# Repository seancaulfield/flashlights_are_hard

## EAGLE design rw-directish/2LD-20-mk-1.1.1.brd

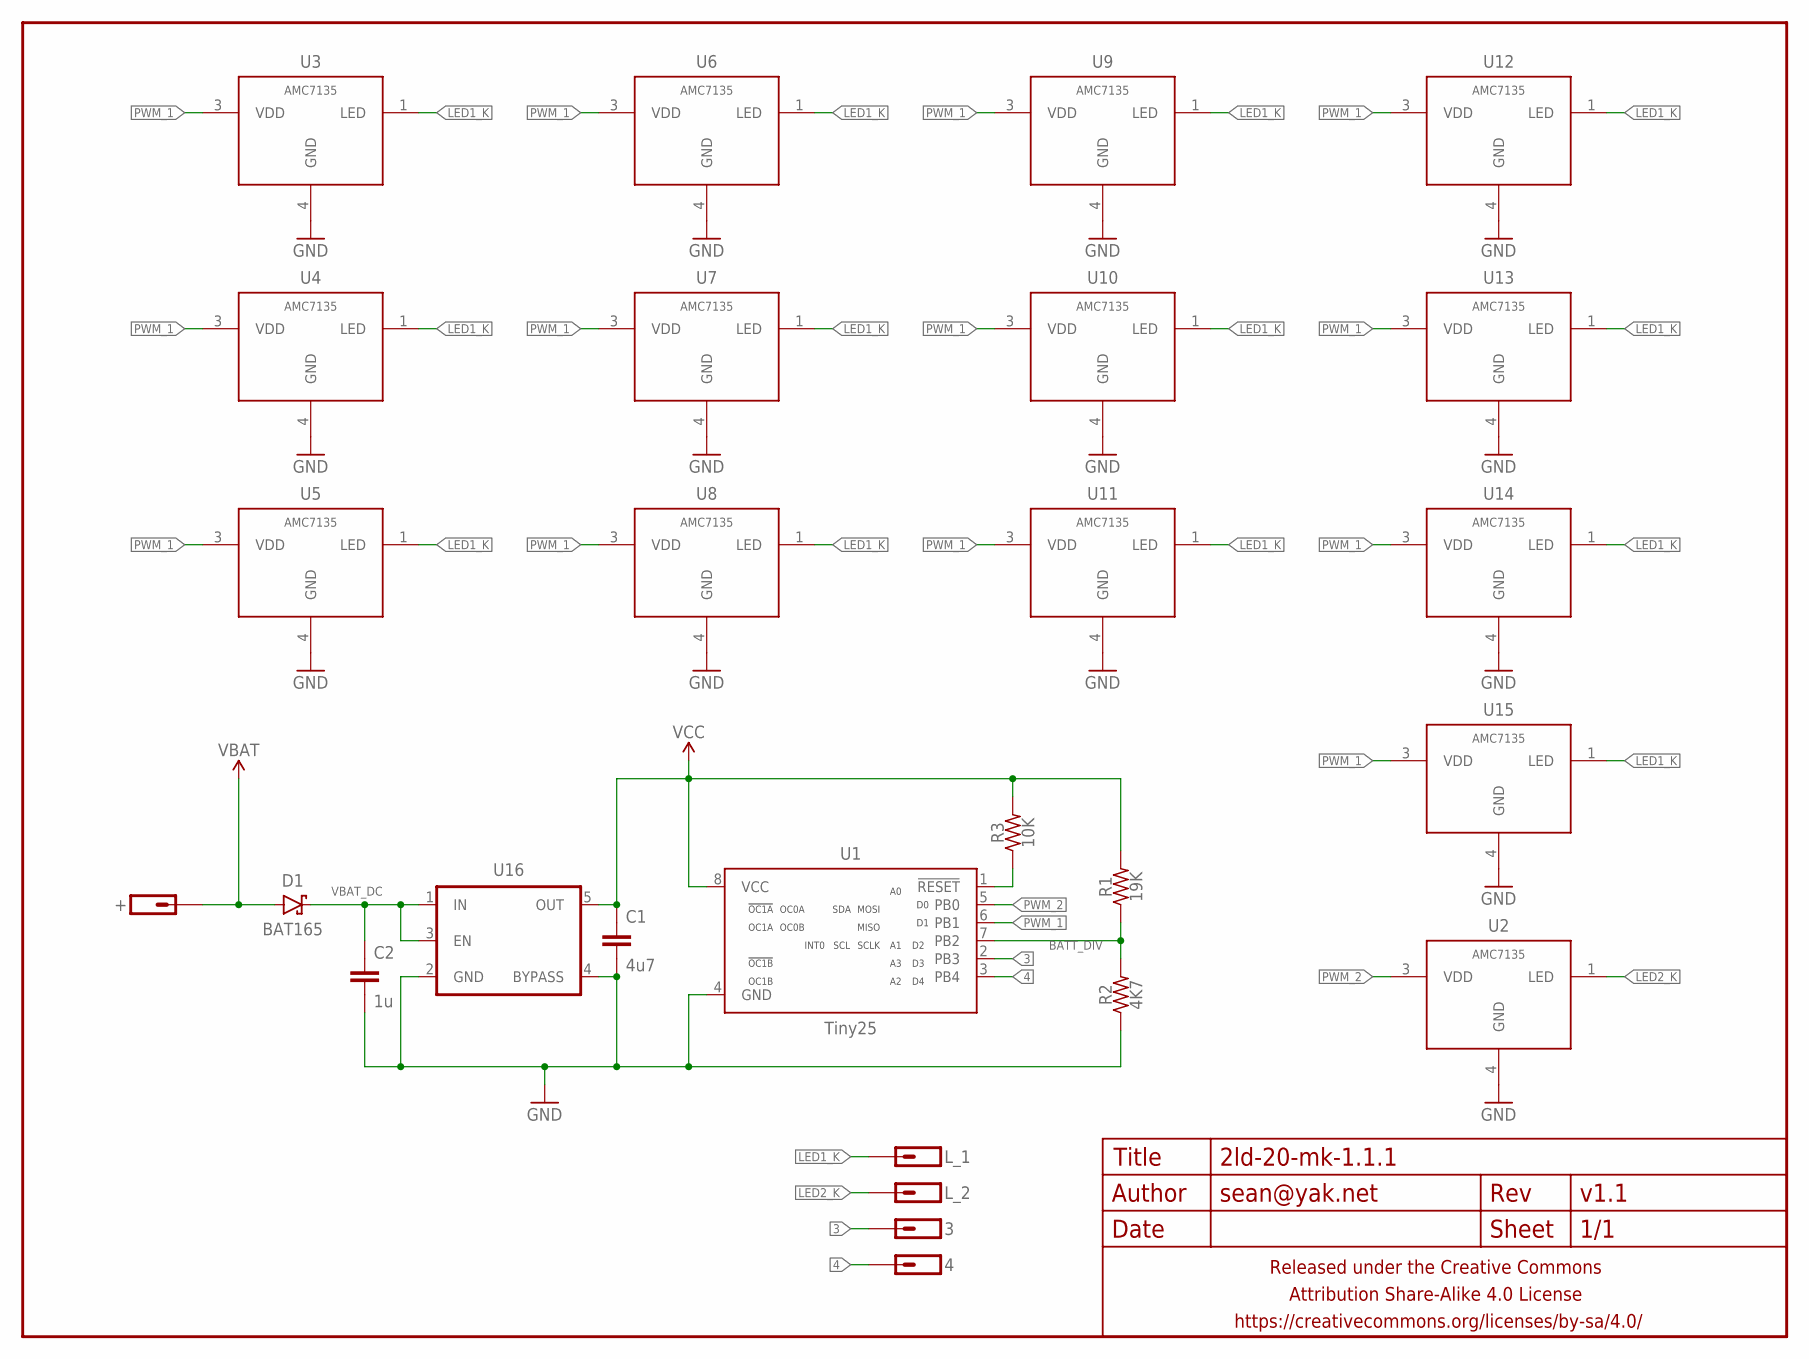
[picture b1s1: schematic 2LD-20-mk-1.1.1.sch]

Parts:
3, 4: M01SMD-0.8MM-DIA-NS; 1X01-SMD-0.8MM-DIA-NS
+: M01PTH-1MM-CIR-NS; 1X01-1MM-CIR-NS
C1: 4u7; C0603-TIGHTER
C2: 1u; C0402
D1: BAT165; SOD323-SCHOTTKY
FRAME1: FRAME-LETTERNO_PACKAGE; DUMMY
L_1: M011X01-0.9MM-CIR; 1X01-0.9MM-CIR
L_2: M01PTH-0.8MM-CIR; 1X01-0.8MM-CIR
R1: 19K; R0402
R2: 4K7; R0402
R3: 10K; R0402
U1: Tiny25; SO08-NARROWER
U2, U3, U4, U5, U6, U7, U8, U9, U10, U11, U12, U13, U14, U15: AMC7135; SOT89-NOTHERM-ROUNDED-LESS
U16: V_REG_SOT-23-5AP2112; SOT23-5

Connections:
3: 3.P$1, U1.2 (PB3)
4: 4.P$1, U1.3 (PB4)
BATT_DIV: R1.1, R2.2, U1.7 (PB2)
GND: C1.2, C2.2, R2.1, U1.4 (GND), U2.4 (GND), U3.4 (GND), U4.4 (GND), U5.4 (GND), U6.4 (GND), U7.4 (GND), U8.4 (GND), U9.4 (GND), U10.4 (GND), U11.4 (GND), U12.4 (GND), U13.4 (GND), U14.4 (GND), U15.4 (GND), U16.2 (GND), U16.4 (BYPASS)
LED1_K: L_1.P$1, U3.1 (LED), U4.1 (LED), U5.1 (LED), U6.1 (LED), U7.1 (LED), U8.1 (LED), U9.1 (LED), U10.1 (LED), U11.1 (LED), U12.1 (LED), U13.1 (LED), U14.1 (LED), U15.1 (LED)
LED2_K: L_2.1, U2.1 (LED)
unnamed: R3.1, U1.1 (!RESET)
PWM_1: U1.6 (PB1), U3.3 (VDD), U4.3 (VDD), U5.3 (VDD), U6.3 (VDD), U7.3 (VDD), U8.3 (VDD), U9.3 (VDD), U10.3 (VDD), U11.3 (VDD), U12.3 (VDD), U13.3 (VDD), U14.3 (VDD), U15.3 (VDD)
PWM_2: U1.5 (PB0), U2.3 (VDD)
VBAT: +.1, D1.A
VBAT_DC: C2.1, D1.C, U16.1 (IN), U16.3 (EN)
VCC: C1.1, R1.2, R3.2, U1.8 (VCC), U16.5 (OUT)

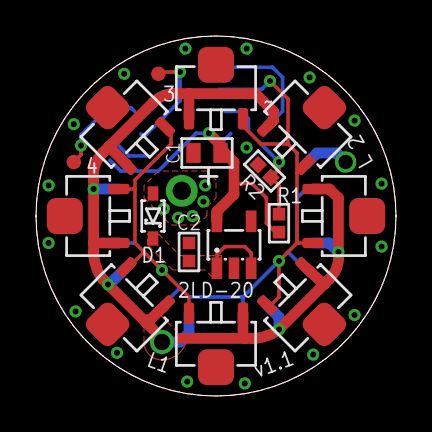
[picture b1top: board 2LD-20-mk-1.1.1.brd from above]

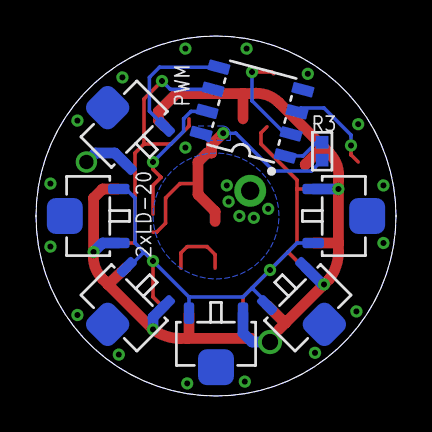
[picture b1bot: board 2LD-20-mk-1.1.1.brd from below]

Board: 2 copper layers, 20.0 x 20.0 mm, 28 parts (8 on the bottom side), 12 nets.

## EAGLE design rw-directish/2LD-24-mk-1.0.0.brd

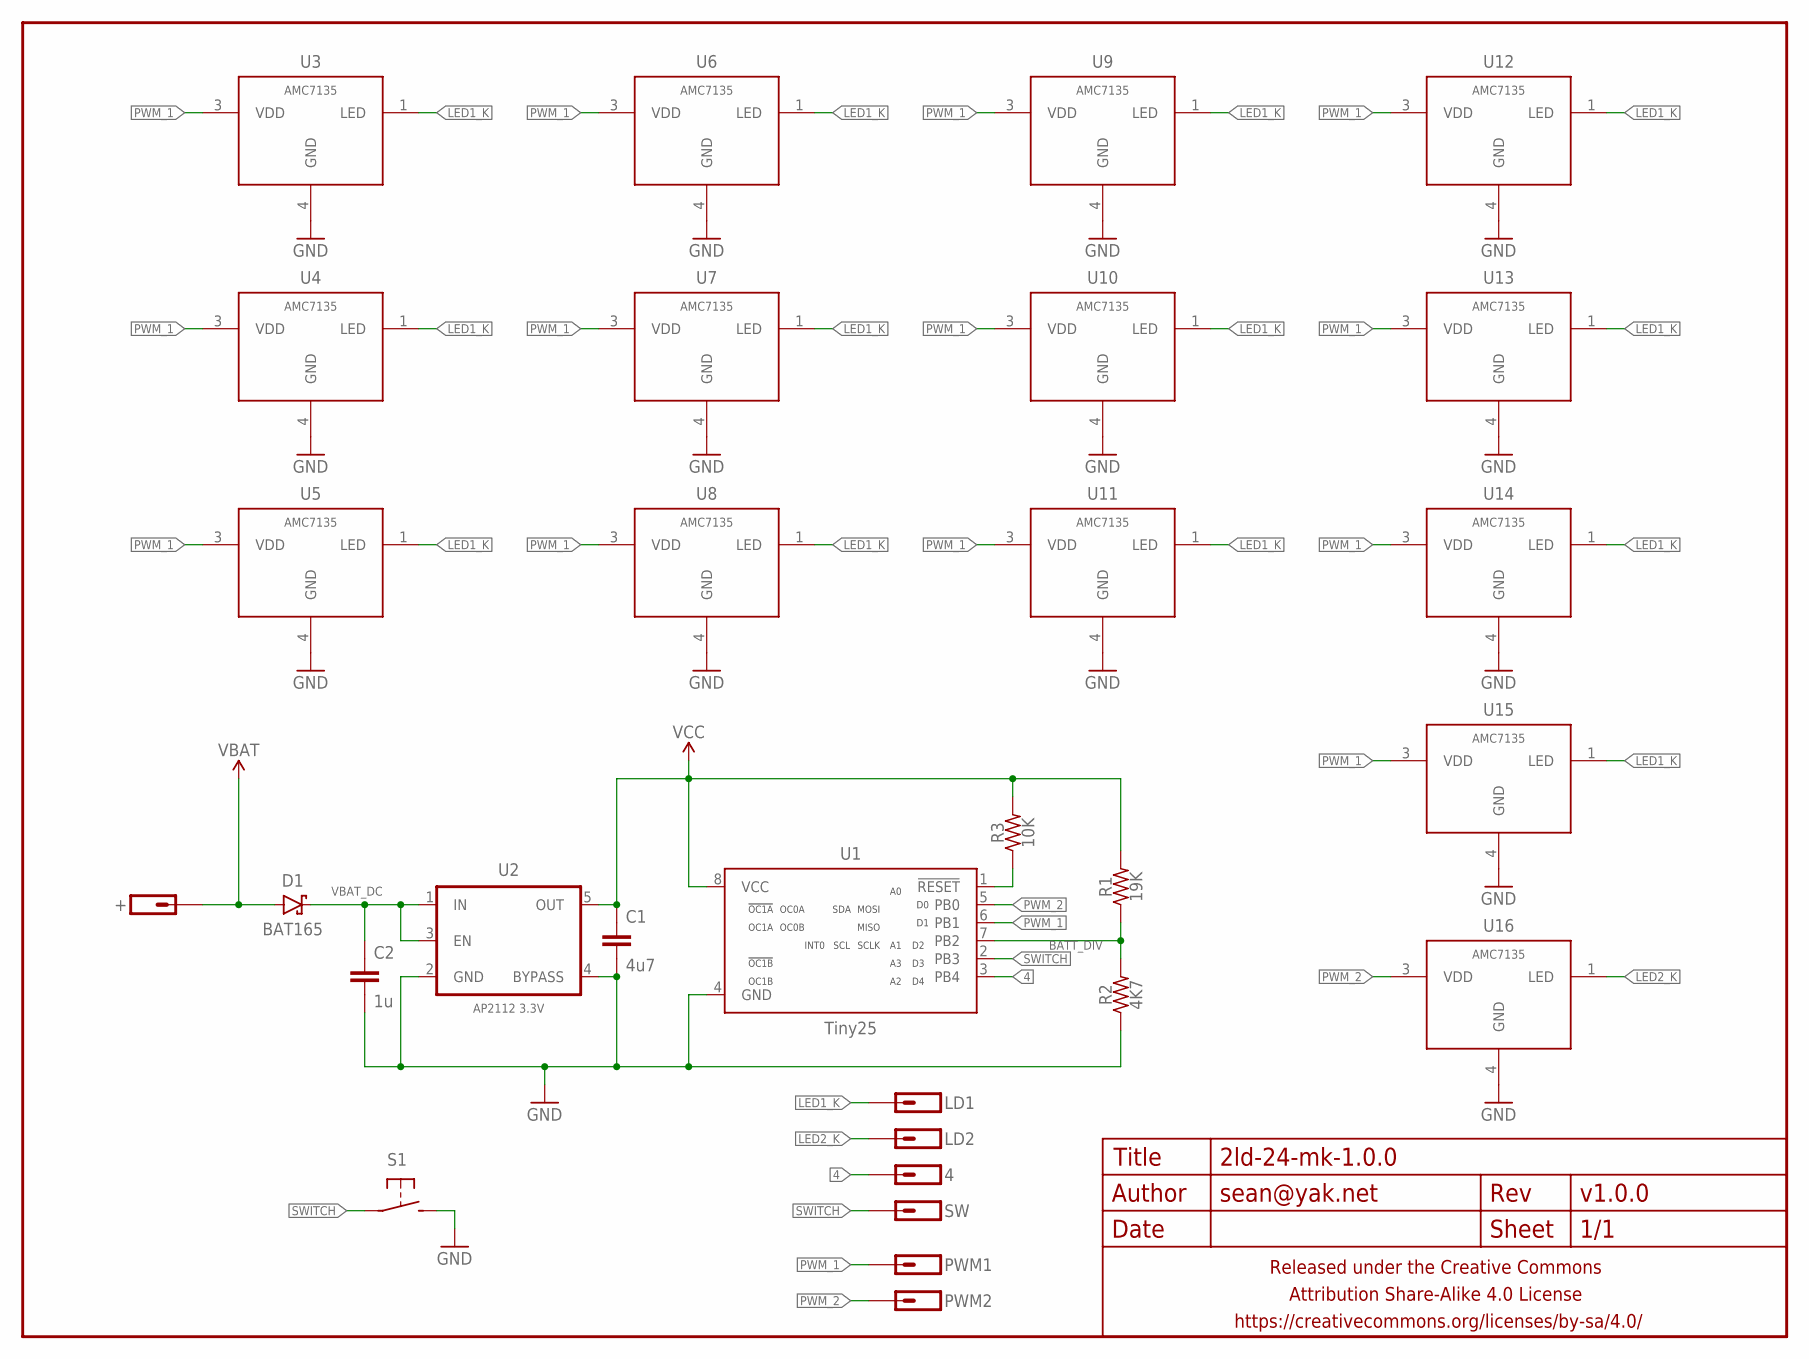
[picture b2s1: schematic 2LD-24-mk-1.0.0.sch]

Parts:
4: M01SMD-0.8MM-DIA-NS; 1X01-SMD-0.8MM-DIA-NS
+: M01PTH-1MM-CIR-NS; 1X01-1MM-CIR-NS
C1: 4u7; C0603-TIGHTER
C2: 1u; C0603-TIGHTER
D1: BAT165; SOD323-SCHOTTKY
FRAME1: FRAME-LETTERNO_PACKAGE; DUMMY
LD1: M01PTH-1MM-CIR-NS; 1X01-1MM-CIR-NS
LD2: M01PTH-0.8MM-CIR; 1X01-0.8MM-CIR
PWM1, PWM2: M01SMD-0.8MM-DIA-NS; 1X01-SMD-0.8MM-DIA-NS
R1: 19K; R0603-TIGHTER
R2: 4K7; R0603-TIGHTER
R3: 10K; R0603-TIGHTER
S1: SPST-NO-TACT3MM-RA-SMALLER; TACTILE-PTH-SIDE-SMALLER
SW: M01SMD-0.8MM-DIA-NS; 1X01-SMD-0.8MM-DIA-NS
U1: Tiny25; SO08-NARROWER
U2: AP2112 3.3V; SOT23-5-SLIM
U3, U4, U5, U6, U7, U8, U9, U10, U11, U12, U13, U14, U15, U16: AMC7135; SOT89-NOTHERM-ROUNDED-LESS

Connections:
4: 4.P$1, U1.3 (PB4)
BATT_DIV: R1.1, R2.2, U1.7 (PB2)
GND: C1.2, C2.2, R2.1, S1.2, U1.4 (GND), U2.2 (GND), U2.4 (BYPASS), U3.4 (GND), U4.4 (GND), U5.4 (GND), U6.4 (GND), U7.4 (GND), U8.4 (GND), U9.4 (GND), U10.4 (GND), U11.4 (GND), U12.4 (GND), U13.4 (GND), U14.4 (GND), U15.4 (GND), U16.4 (GND)
LED1_K: LD1.1, U3.1 (LED), U4.1 (LED), U5.1 (LED), U6.1 (LED), U7.1 (LED), U8.1 (LED), U9.1 (LED), U10.1 (LED), U11.1 (LED), U12.1 (LED), U13.1 (LED), U14.1 (LED), U15.1 (LED)
LED2_K: LD2.1, U16.1 (LED)
unnamed: R3.1, U1.1 (!RESET)
PWM_1: PWM1.P$1, U1.6 (PB1), U3.3 (VDD), U4.3 (VDD), U5.3 (VDD), U6.3 (VDD), U7.3 (VDD), U8.3 (VDD), U9.3 (VDD), U10.3 (VDD), U11.3 (VDD), U12.3 (VDD), U13.3 (VDD), U14.3 (VDD), U15.3 (VDD)
PWM_2: PWM2.P$1, U1.5 (PB0), U16.3 (VDD)
SWITCH: S1.1, SW.P$1, U1.2 (PB3)
VBAT: +.1, D1.A
VBAT_DC: C2.1, D1.C, U2.1 (IN), U2.3 (EN)
VCC: C1.1, R1.2, R3.2, U1.8 (VCC), U2.5 (OUT)

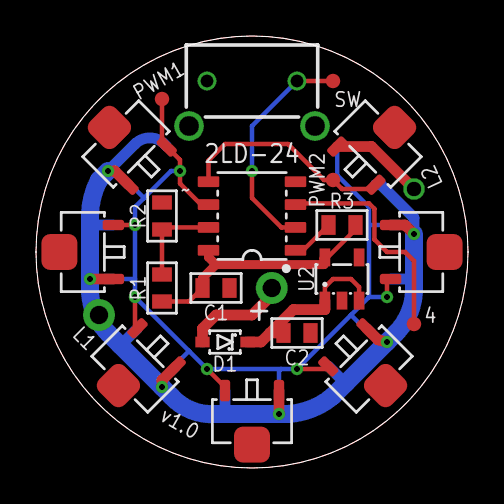
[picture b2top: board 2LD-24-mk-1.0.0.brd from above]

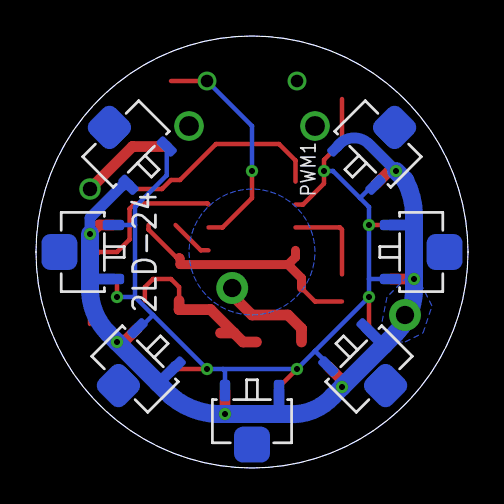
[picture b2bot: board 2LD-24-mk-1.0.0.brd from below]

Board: 2 copper layers, 24.0 x 24.0 mm, 31 parts (7 on the bottom side), 12 nets.

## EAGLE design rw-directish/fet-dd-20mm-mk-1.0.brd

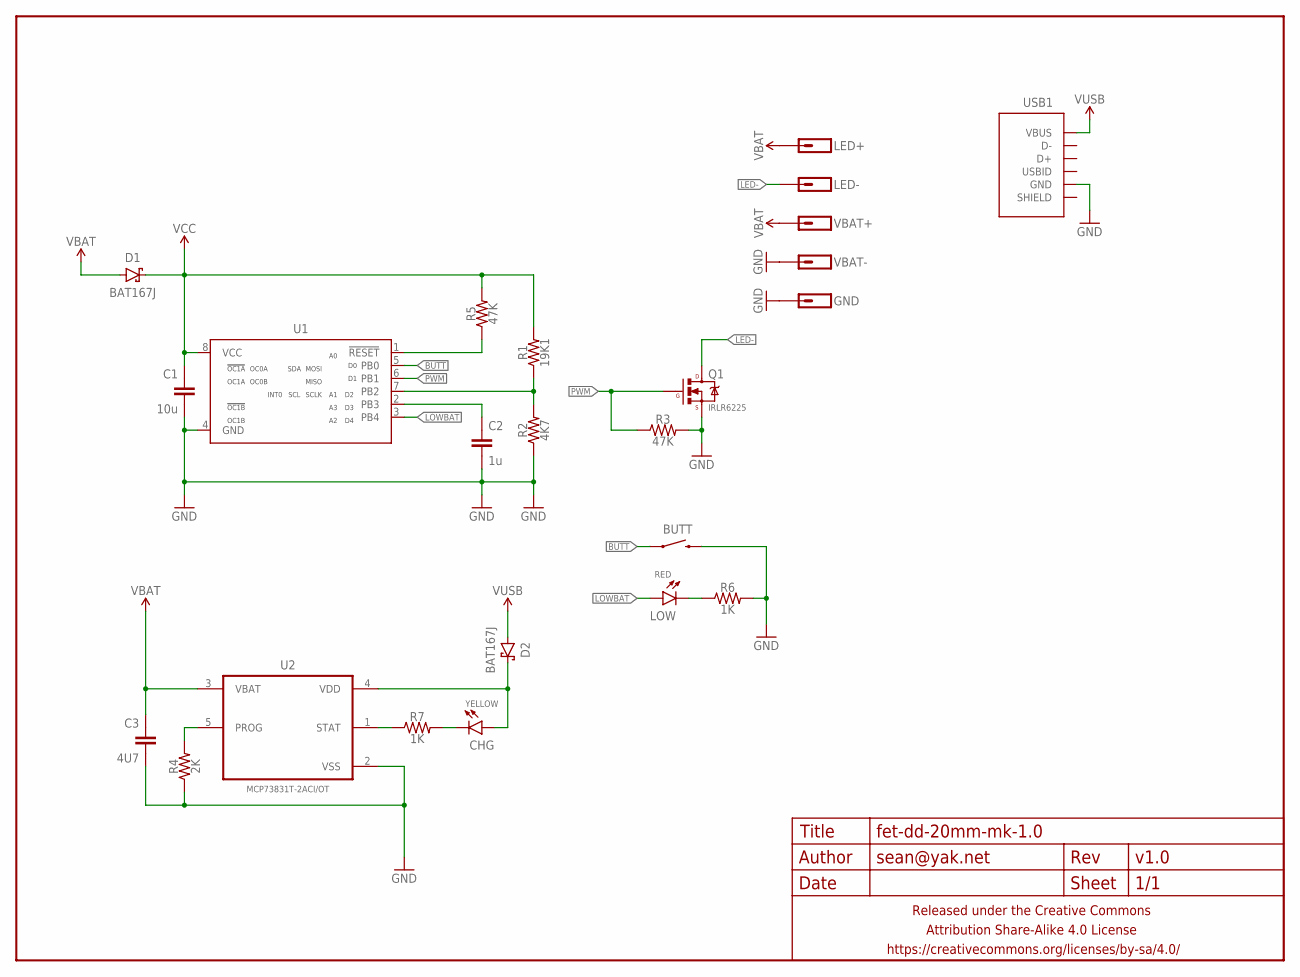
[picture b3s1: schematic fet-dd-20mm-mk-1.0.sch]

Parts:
BUTT: SWITCH-MOMENTARY-2PTH-RA; TACTILE-PTH-SIDE
C1: 10u; C0603-TIGHTER
C2: 1u; C0603-TIGHTER
C3: 4U7; C0603-TIGHTER
CHG: YELLOW; LED-0603-TIGHT
D1, D2: BAT167J; SOD323-SCHOTTKY
FRAME1: FRAME-LETTERNO_PACKAGE; DUMMY
GND: M01PTH_2MM; 1X01_2MM
LED+: M01PTH_2MM; 1X01_2MM
LED-: M01PTH_2MM; 1X01_2MM
LOW: RED; LED-0603-TIGHT
Q1: IRLR6225; SOT223-CLOSER
R1: 19K1; R0603-TIGHTER
R2: 4K7; R0603-TIGHTER
R3, R5: 47K; R0402
R4: 2K; R0603-TIGHTER
R6, R7: 1K; R0603-TIGHTER
U1: ATTINY13SOIC-NARROWPADS; SO08-NARROWER
U2: MCP73831T-2ACI/OT; SOT95P280X145-5N
USB1: USB-AB-SHIELDFCI-10118193-USB-MICRO-B; FCI-10118193-USB-MICRO-B
VBAT+: M01NOSTOP-CANTSTOP-DONTKNOWHOWTOSTOP; 1X01_SMD_NOSTOP_NOSILK
VBAT-: M01NOT-A-VIA-NOPE; 1X01_NOSILK_NOSTOP

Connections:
BUTT: BUTT.1, U1.5 (PB0)
GND: BUTT.2, C1.2, C2.2, C3.2, GND.1, Q1.3 (S), R2.1, R3.2, R4.1, R6.2, U1.4 (GND), U2.2 (VSS), USB1.5 (GND), VBAT-.P$1
LED-: LED-.1, Q1.2 (D), Q1.4 (D)
LOWBAT: LOW.A, U1.3 (PB4)
unnamed: R5.1, U1.1 (!RESET)
unnamed: R1.1, R2.2, U1.7 (PB2)
unnamed: C2.1, U1.2 (PB3)
unnamed: R4.2, U2.5 (PROG)
unnamed: CHG.A, D2.C, U2.4 (VDD)
unnamed: LOW.C, R6.1
unnamed: CHG.C, R7.2
unnamed: R7.1, U2.1 (STAT)
PWM: Q1.1 (G), R3.1, U1.6 (PB1)
VBAT: C3.1, D1.A, LED+.1, U2.3 (VBAT), VBAT+.1
VCC: C1.1, D1.C, R1.2, R5.2, U1.8 (VCC)
VUSB: D2.A, USB1.1 (VBUS)

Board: 2 copper layers, 25 parts (1 on the bottom side), 16 nets, no tracks yet.

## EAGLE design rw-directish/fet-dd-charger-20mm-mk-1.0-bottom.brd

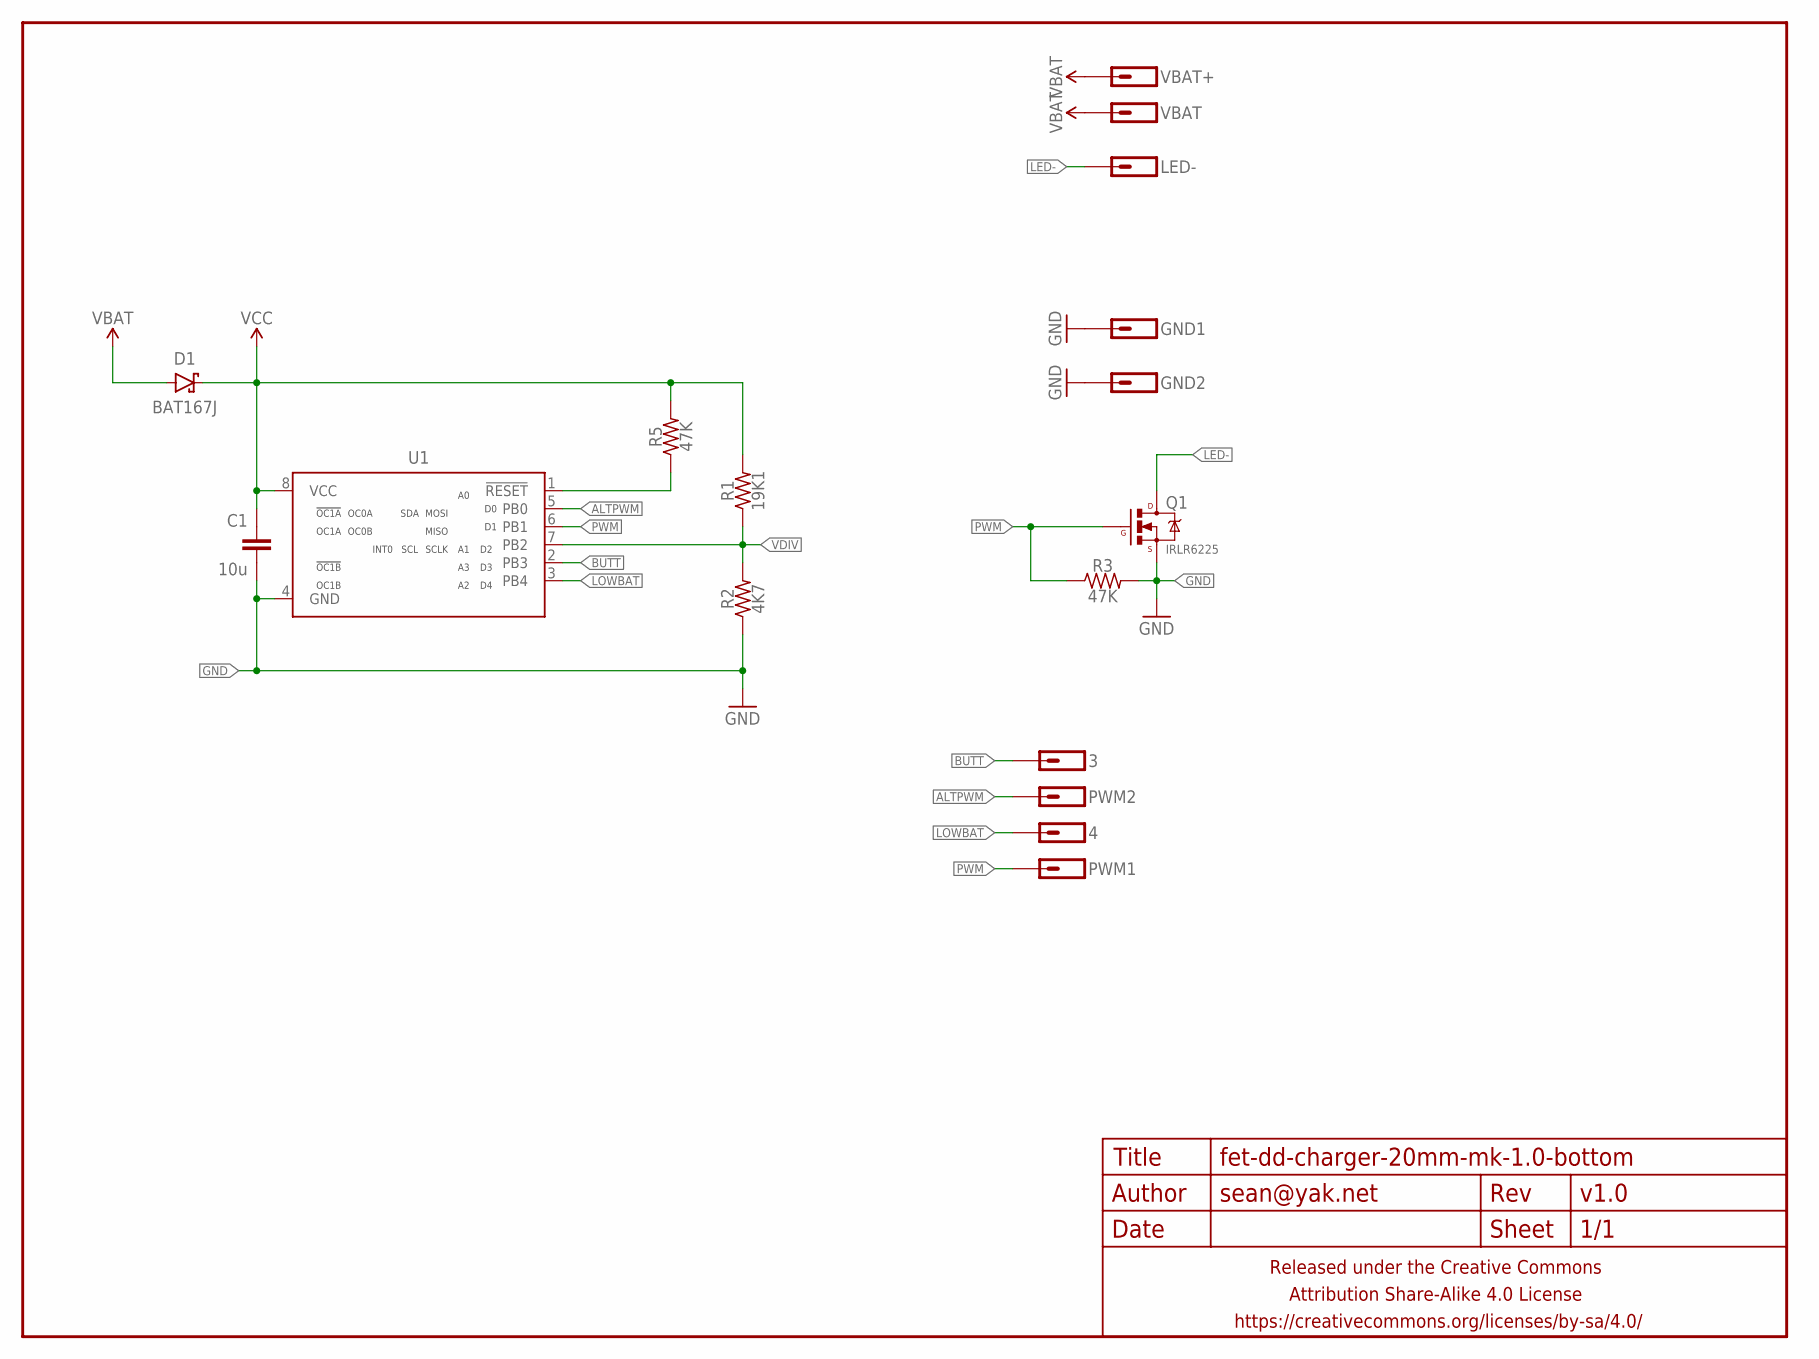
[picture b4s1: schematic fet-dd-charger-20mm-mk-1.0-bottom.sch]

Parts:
3, 4: M01SMD-1MM-DIA-NS; 1X01-SMD-1MM-DIA-NS
C1: 10u; C0603-TIGHTER
D1: BAT167J; SOD123-SCHOTTKY
FRAME1: FRAME-LETTERNO_PACKAGE; DUMMY
GND1, GND2: M01PTH_2MM; 1X01_2MM
LED-: M01PTH_2MM; 1X01_2MM
PWM1, PWM2: M01SMD-1MM-DIA-NS; 1X01-SMD-1MM-DIA-NS
Q1: IRLR6225; POWERPACK-SO-8
R1: 19K1; R0603-TIGHTER
R2: 4K7; R0603-TIGHTER
R3, R5: 47K; R0603-TIGHTER
U1: ATTINY13SOIC-NARROWPADS; SO08-NARROWER
VBAT: M01PTH_2MM; 1X01_2MM
VBAT+: M01NOSTOP-CANTSTOP-DONTKNOWHOWTOSTOP; 1X01_SMD_NOSTOP_NOSILK

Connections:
ALTPWM: PWM2.P$1, U1.5 (PB0)
BUTT: 3.P$1, U1.2 (PB3)
GND: C1.2, GND1.1, GND2.1, Q1.1 (S), Q1.2 (S), Q1.3 (S), R2.1, R3.2, U1.4 (GND)
LED-: LED-.1, Q1.5678 (D)
LOWBAT: 4.P$1, U1.3 (PB4)
unnamed: R5.1, U1.1 (!RESET)
PWM: PWM1.P$1, Q1.4 (G), R3.1, U1.6 (PB1)
VBAT: D1.A, VBAT.1, VBAT+.1
VCC: C1.1, D1.C, R1.2, R5.2, U1.8 (VCC)
VDIV: R1.1, R2.2, U1.7 (PB2)

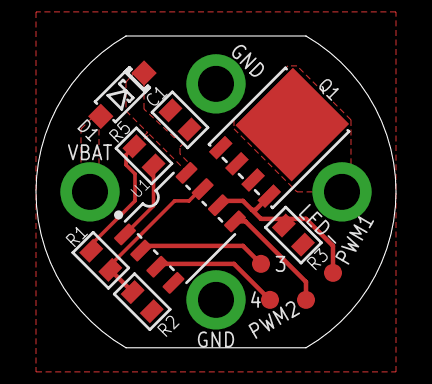
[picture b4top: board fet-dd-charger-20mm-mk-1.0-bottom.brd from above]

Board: 2 copper layers, 20.0 x 17.3 mm, 18 parts (1 on the bottom side), 10 nets.

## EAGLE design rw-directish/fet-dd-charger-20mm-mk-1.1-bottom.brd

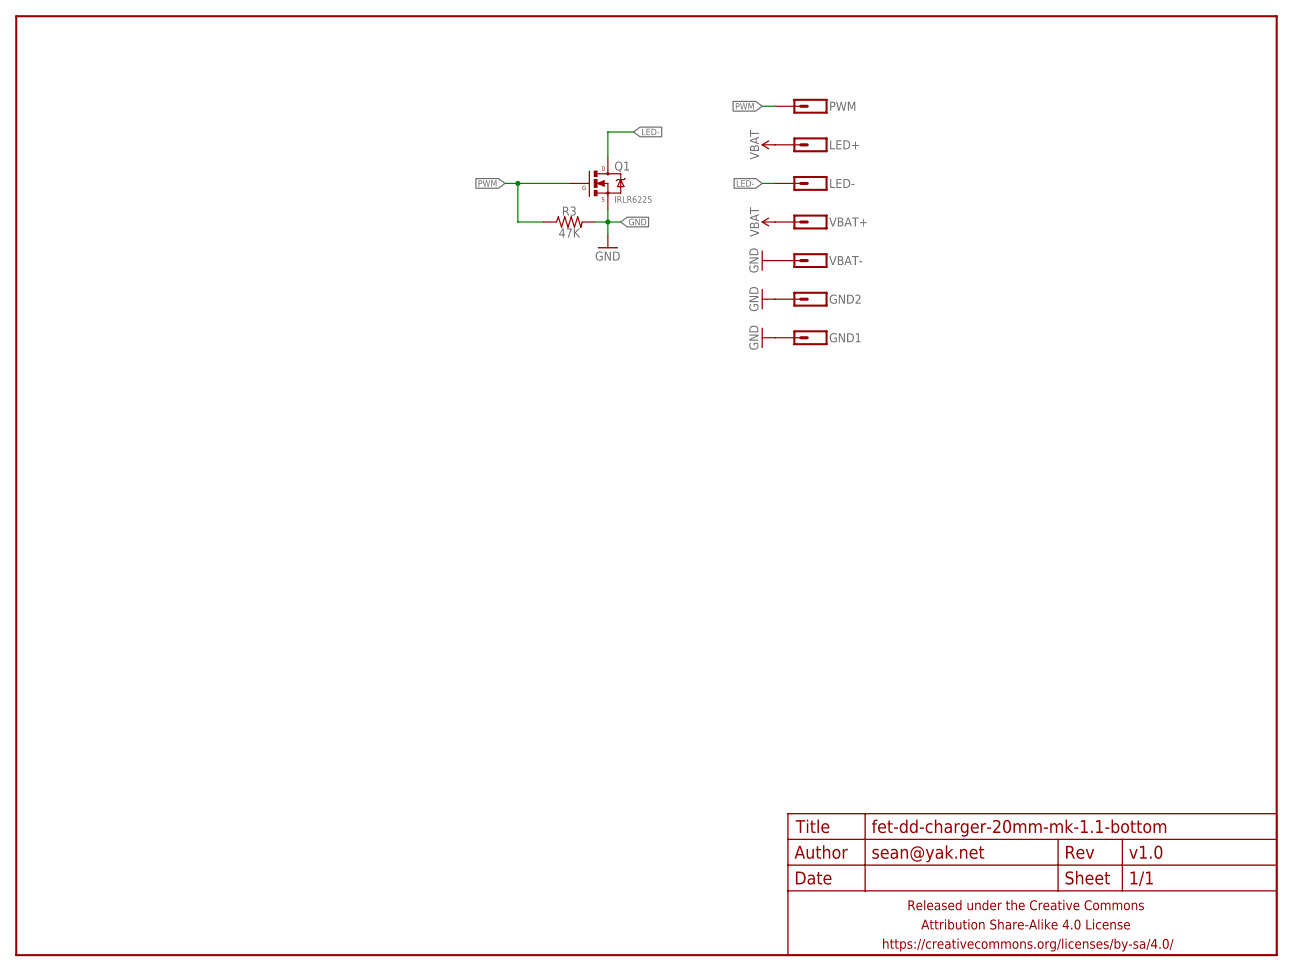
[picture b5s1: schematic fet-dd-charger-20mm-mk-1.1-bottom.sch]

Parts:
FRAME1: FRAME-LETTERNO_PACKAGE; DUMMY
GND1, GND2: M01PTH_2MM; 1X01_2MM
LED+: M01PTH_2MM; 1X01_2MM
LED-: M01PTH_2MM; 1X01_2MM
PWM: M01SMD-1MM-CIR; 1X01-SMD-1MM-DIA
Q1: IRLR6225; SOT223-CLOSER
R3: 47K; R0603-TIGHTER
VBAT+: M01NOSTOP-CANTSTOP-DONTKNOWHOWTOSTOP; 1X01_SMD_NOSTOP_NOSILK
VBAT-: M01NOT-A-VIA-NOPE; 1X01_NOSILK_NOSTOP

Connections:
GND: GND1.1, GND2.1, Q1.3 (S), R3.2, VBAT-.P$1
LED-: LED-.1, Q1.2 (D), Q1.4 (D)
PWM: PWM.P$1, Q1.1 (G), R3.1
VBAT: LED+.1, VBAT+.1

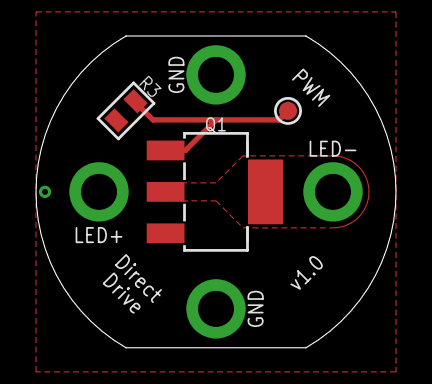
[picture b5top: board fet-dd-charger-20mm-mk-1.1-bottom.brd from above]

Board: 2 copper layers, 20.0 x 17.3 mm, 10 parts (1 on the bottom side), 4 nets.

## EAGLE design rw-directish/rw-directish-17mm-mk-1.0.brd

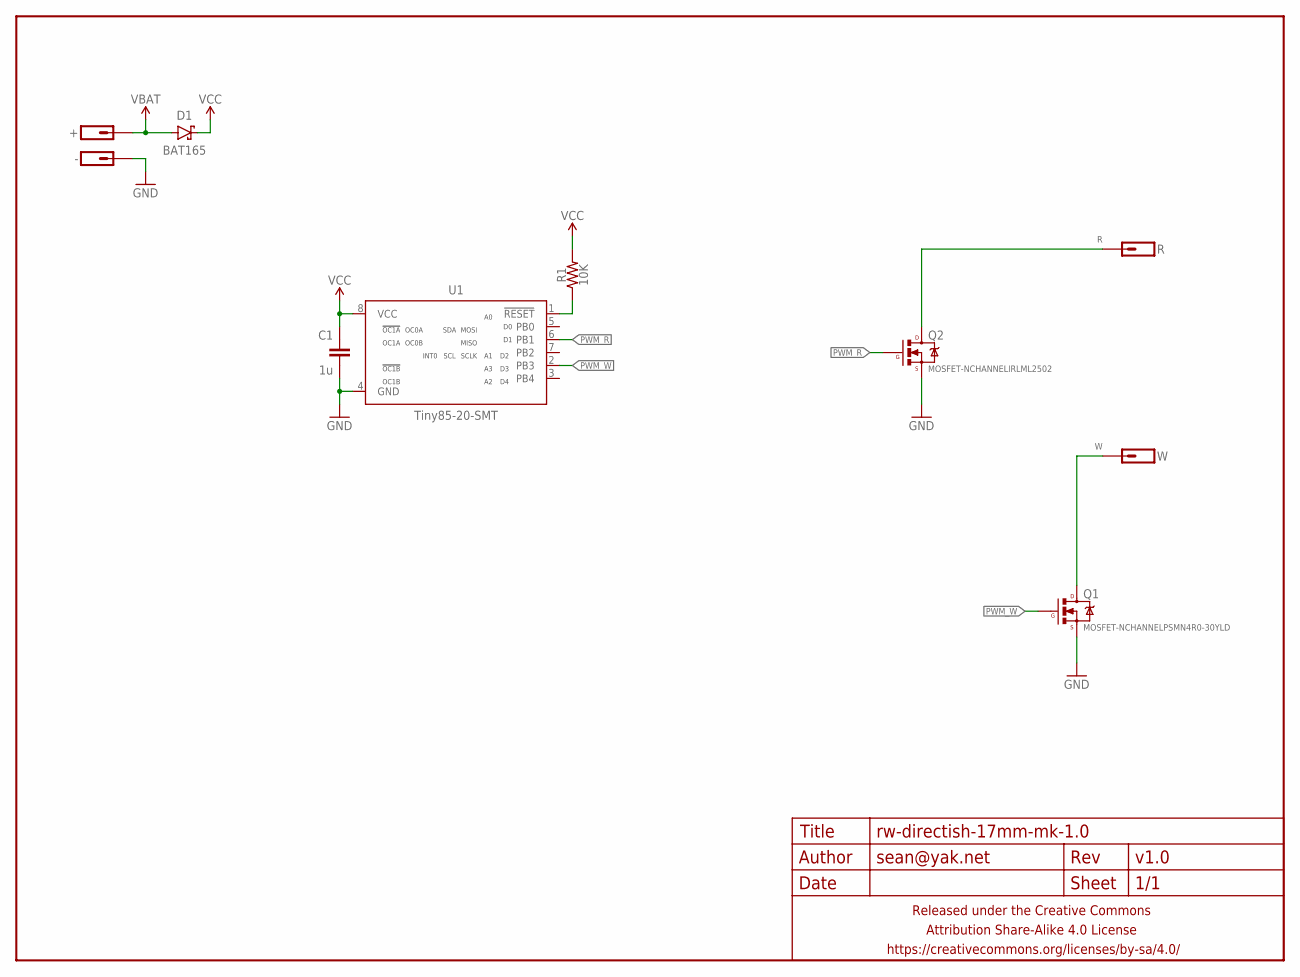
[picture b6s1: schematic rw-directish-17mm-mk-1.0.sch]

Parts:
+: M01PTH-1.2MM-NS; 1X01-1.2MM-NS
-: M01NOT-A-VIA-NOPE; 1X01_NOSILK_NOSTOP
C1: 1u; C0402
D1: BAT165; SOD323-SCHOTTKY
FRAME1: FRAME-LETTERNO_PACKAGE; DUMMY
Q1: MOSFET-NCHANNELPSMN4R0-30YLD; LFPAK56
Q2: MOSFET-NCHANNELIRLML2502; SOT23
R: M01SMD-1.25MM-DIA; 1X01-SMD-1.25MM-DIA-NS
R1: 10K; R0402
U1: Tiny85-20-SMT; SO08-EIAJ
W: M01SMD-1.25MM-DIA; 1X01-SMD-1.25MM-DIA-NS

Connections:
GND: -.P$1, C1.2, Q1.1 (S), Q1.2 (S), Q1.3 (S), Q2.2 (S), U1.4 (GND)
unnamed: R1.1, U1.1 (!RESET)
PWM_R: Q2.1 (G), U1.6 (PB1)
PWM_W: Q1.4 (G), U1.2 (PB3)
R: Q2.3 (D), R.P$1
VBAT: +.P$1, D1.A
VCC: C1.1, D1.C, R1.2, U1.8 (VCC)
W: Q1.MB@1 (D), Q1.MB@2 (D), W.P$1

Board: 2 copper layers, 11 parts (1 on the bottom side), 8 nets, no tracks yet.

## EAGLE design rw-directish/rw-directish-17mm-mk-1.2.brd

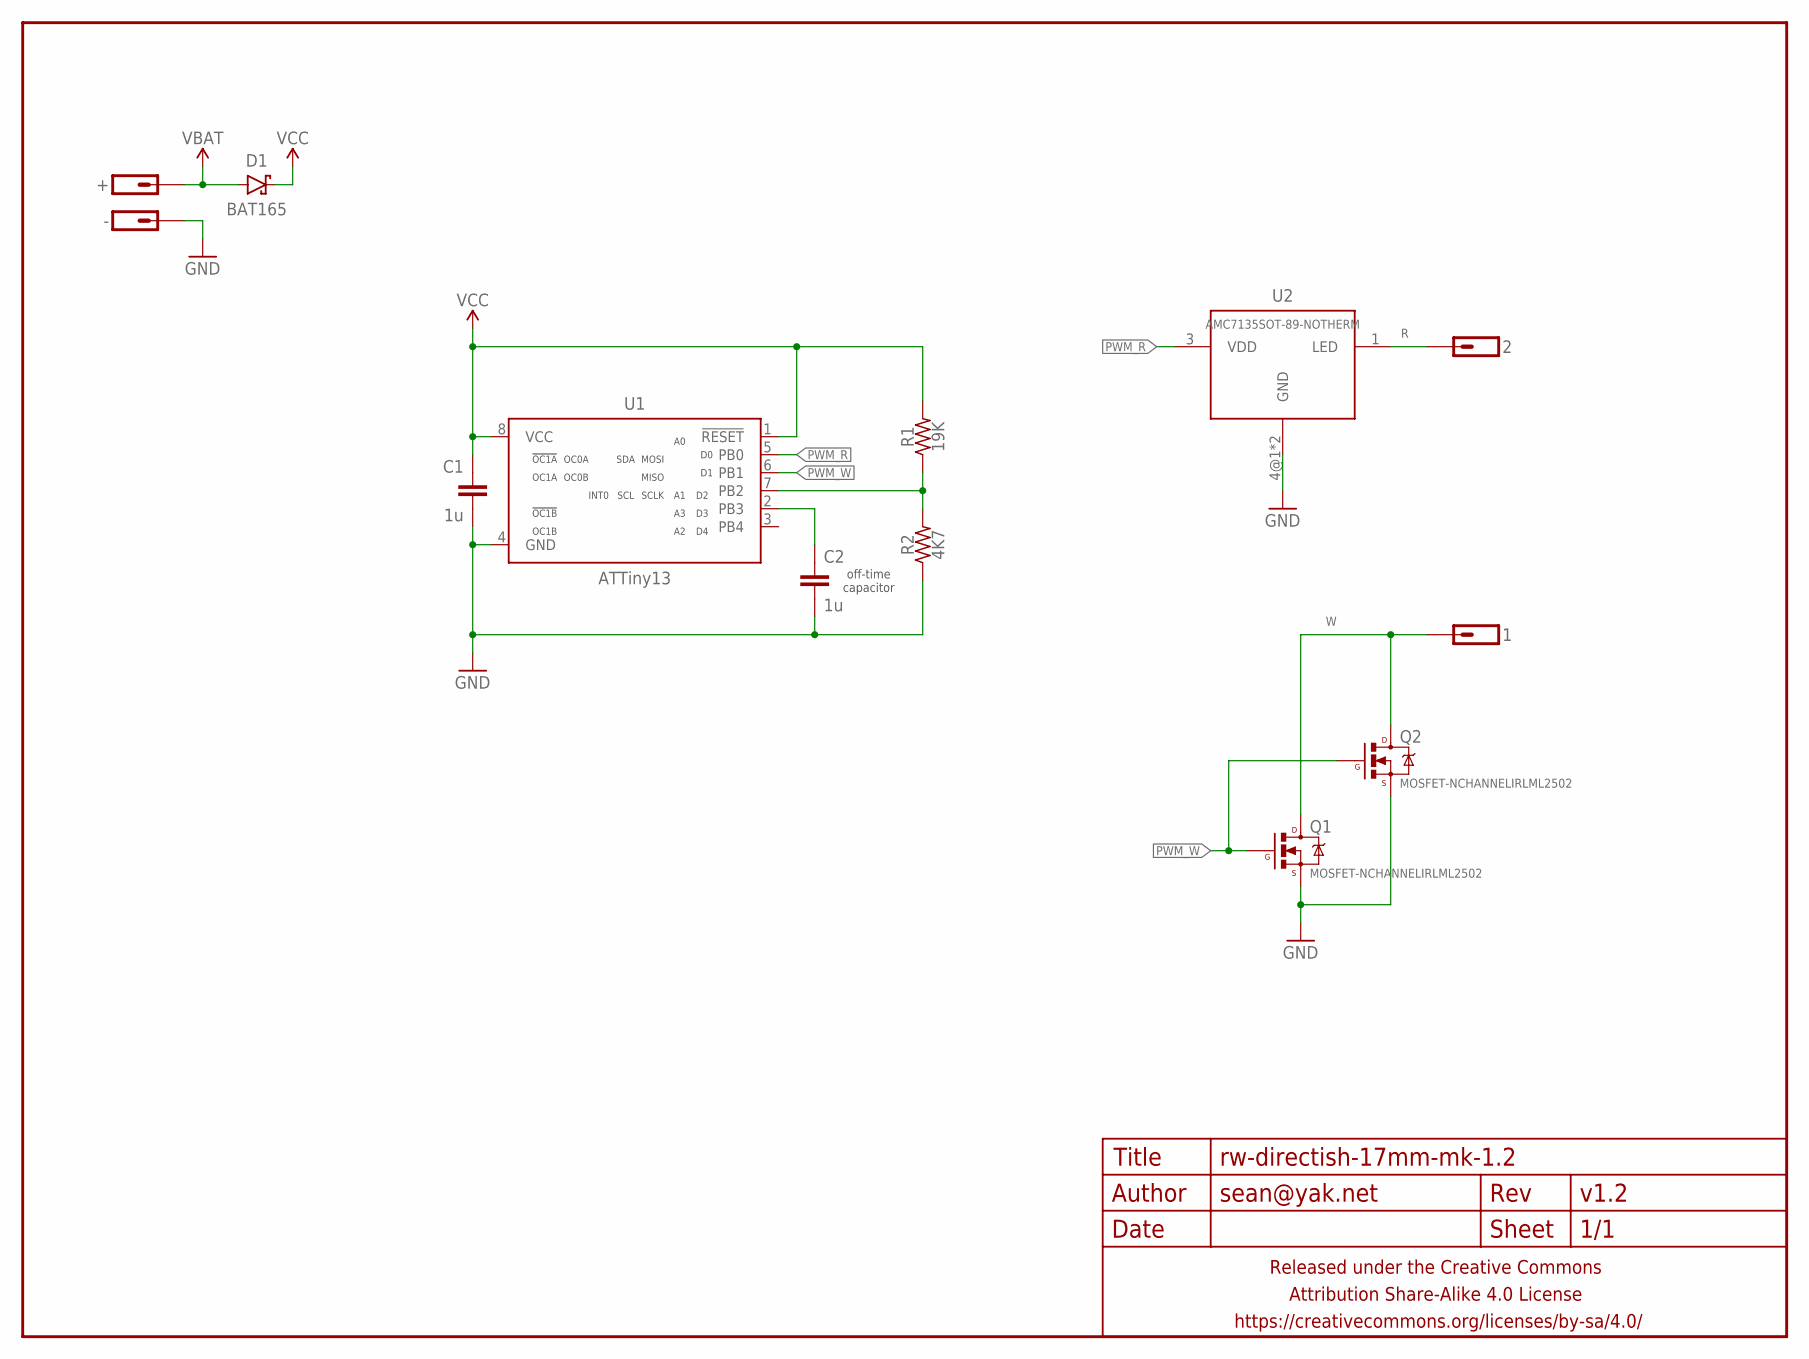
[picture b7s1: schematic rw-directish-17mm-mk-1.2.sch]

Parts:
1, 2: M01SMD-1.25MM-DIA; 1X01-SMD-1.25MM-DIA-NS
+: M01PTH-1.2MM-NS; 1X01-1.2MM-NS
-: M01NOT-A-VIA-NOPE; 1X01_NOSILK_NOSTOP
C1: 1u; C0603-TIGHTER
C2: 1u; C0402
D1: BAT165; SOD323-SCHOTTKY
FRAME1: FRAME-LETTERNO_PACKAGE; DUMMY
Q1, Q2: MOSFET-NCHANNELIRLML2502; SOT23
R1: 19K; R0402
R2: 4K7; R0402
U1: ATTiny13; SO08-NARROWER
U2: AMC7135SOT-89-NOTHERM; SOT89-NOTHERM

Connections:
GND: -.P$1, C1.2, C2.2, Q1.2 (S), Q2.2 (S), R2.1, U1.4 (GND), U2.4@1 (GND), U2.4@2 (GND)
unnamed: R1.1, R2.2, U1.7 (PB2)
unnamed: C2.1, U1.2 (PB3)
PWM_R: U1.5 (PB0), U2.3 (VDD)
PWM_W: Q1.1 (G), Q2.1 (G), U1.6 (PB1)
R: 2.P$1, U2.1 (LED)
VBAT: +.P$1, D1.A
VCC: C1.1, D1.C, R1.2, U1.1 (!RESET), U1.8 (VCC)
W: 1.P$1, Q1.3 (D), Q2.3 (D)

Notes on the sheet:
off-time capacitor

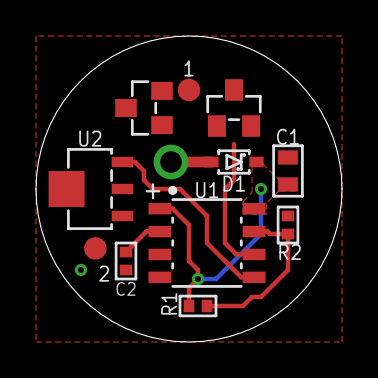
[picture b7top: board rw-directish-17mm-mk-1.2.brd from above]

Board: 2 copper layers, 17.0 x 17.0 mm, 14 parts (1 on the bottom side), 9 nets.

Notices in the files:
parts and their libraries:
a_parts: Released under the Creative Commons Attribution Share-Alike 4.0 License
a_parts: https://creativecommons.org/licenses/by-sa/4.0
a_parts: Released under the Creative Commons
